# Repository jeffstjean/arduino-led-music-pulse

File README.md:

# Arduino Led Music Pulse

Controls an LED light-strip using an Arduino to pulse to the beat of a input from a 3.5mm audio device
[View the Demo.](https://youtu.be/wHUdtZS7I78)

## Getting Started
---

### Prerequisites

You will need to download the following libraries:
* [ArduinoFFT](https://github.com/kosme/arduinoFFT)
* [Adafruit_NeoPixel](https://github.com/adafruit/Adafruit_NeoPixel)
* [MicroSmooth](https://github.com/asheeshr/Microsmooth)

### Hardware

Read [HARDWARE.md](HARDWARE.md) to make sure you are using the correct parts.

### Schematic

Please reference [audio-in-schematic.png](audio-in-schematic.png) to connect the audio-in circuit correctly.  
For the light strip: 5V connects to Arduino/external 5V, GND to Arduino/external GND and DATA to Arduino's Digital Pin 6.

### Installing

Once you have downloaded the files and libraries, upload the code to your Arduino.  
You can then plug in your phone or computer to the 3.5mm audio jack.  
Provde power to your arduino and begin playing music.  

## Authors

* **Jeff St. Jean** - *Initial work* - [JeffStJean](https://github.com/jeffstjean)

## License

This project is licensed under the GNU v3 License - see the [LICENSE](LICENSE) file for details

## Acknowledgments

[Devon Crawford](https://www.youtube.com/channel/UCDrekHmOnkptxq3gUU0IyfA) for the inspiration for this project!  
[This StackExchange post](https://arduino.stackexchange.com/questions/25483/audio-input-into-a0) for help getting the voltage divider correctly wired.  
[This Arduino Forum post](https://forum.arduino.cc/index.php?topic=508537.0) for guidance.

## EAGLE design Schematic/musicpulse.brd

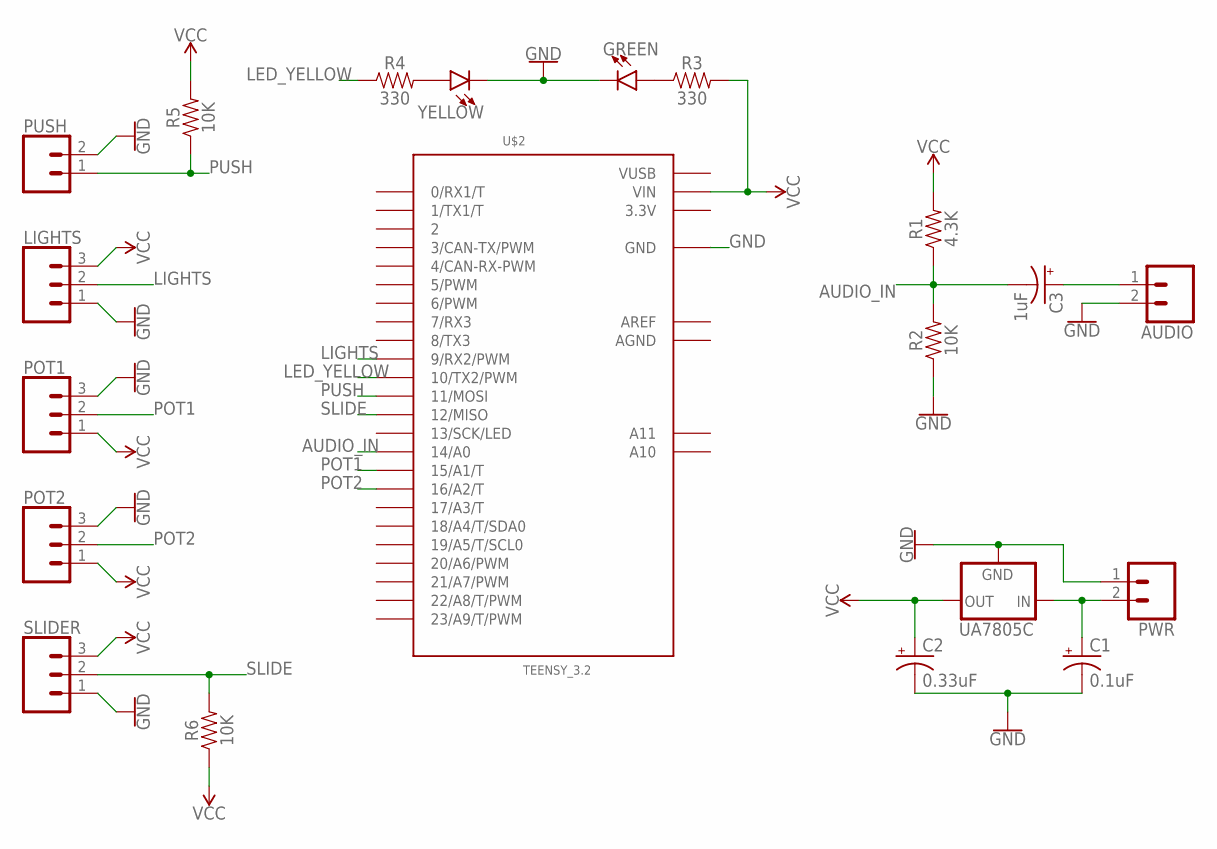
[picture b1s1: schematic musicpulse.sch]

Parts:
AUDIO: CONN_02; 1X02
C1: 0.1uF; CPOL-RADIAL-2.5MM-5MM
C2: 0.33uF; CPOL-RADIAL-2.5MM-5MM
C3: 1uF; CPOL-RADIAL-2.5MM-5MM
GREEN: LED-3MM-NO_SILK; LED_3MM-NS
LIGHTS: CONN_03; 1X03
POT1, POT2: CONN_03; 1X03
PUSH: CONN_02; 1X02
PWR: CONN_02; 1X02
R1: 4.3K; AXIAL-0.3
R2, R5, R6: 10K; AXIAL-0.3
R3, R4: 330; AXIAL-0.3
SLIDER: CONN_03; 1X03
U$2: TEENSY_3.2; TEENSY_3.0-3.2&LC_DIL+4
UA7805C: V_REG_78XXSINK; TO220-IGO
YELLOW: LED-3MM-NO_SILK; LED_3MM-NS

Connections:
3.3V: U$2.3.3V
AGND: U$2.AGND
AREF: U$2.AREF
AUDIO_IN: C3.2 (-), R1.P$1 (1), R2.P$2 (2), U$2.14/A0
GND: AUDIO.2, C1.2 (-), C2.2 (-), GREEN.K (C), LIGHTS.1, POT1.3, POT2.3, PUSH.2, PWR.1, R2.P$1 (1), SLIDER.1, U$2.GND, UA7805C.GND, YELLOW.K (C)
LED_YELLOW: R4.P$1 (1), U$2.10 (10/TX2/PWM)
LIGHTS: LIGHTS.2, U$2.9 (9/RX2/PWM)
unnamed: C1.1 (+), PWR.2, UA7805C.IN
unnamed: R4.P$2 (2), YELLOW.A
unnamed: GREEN.A, R3.P$1 (1)
unnamed: AUDIO.1, C3.1 (+)
POT1: POT1.2, U$2.15/A1 (15/A1/T)
POT2: POT2.2, U$2.16/A2 (16/A2/T)
PUSH: PUSH.1, R5.P$1 (1), U$2.11 (11/MOSI)
SLIDE: R6.P$2 (2), SLIDER.2, U$2.12 (12/MISO)
VCC: C2.1 (+), LIGHTS.3, POT1.1, POT2.1, R1.P$2 (2), R3.P$2 (2), R5.P$2 (2), R6.P$1 (1), SLIDER.3, U$2.VIN, UA7805C.OUT
VUSB: U$2.VUSB

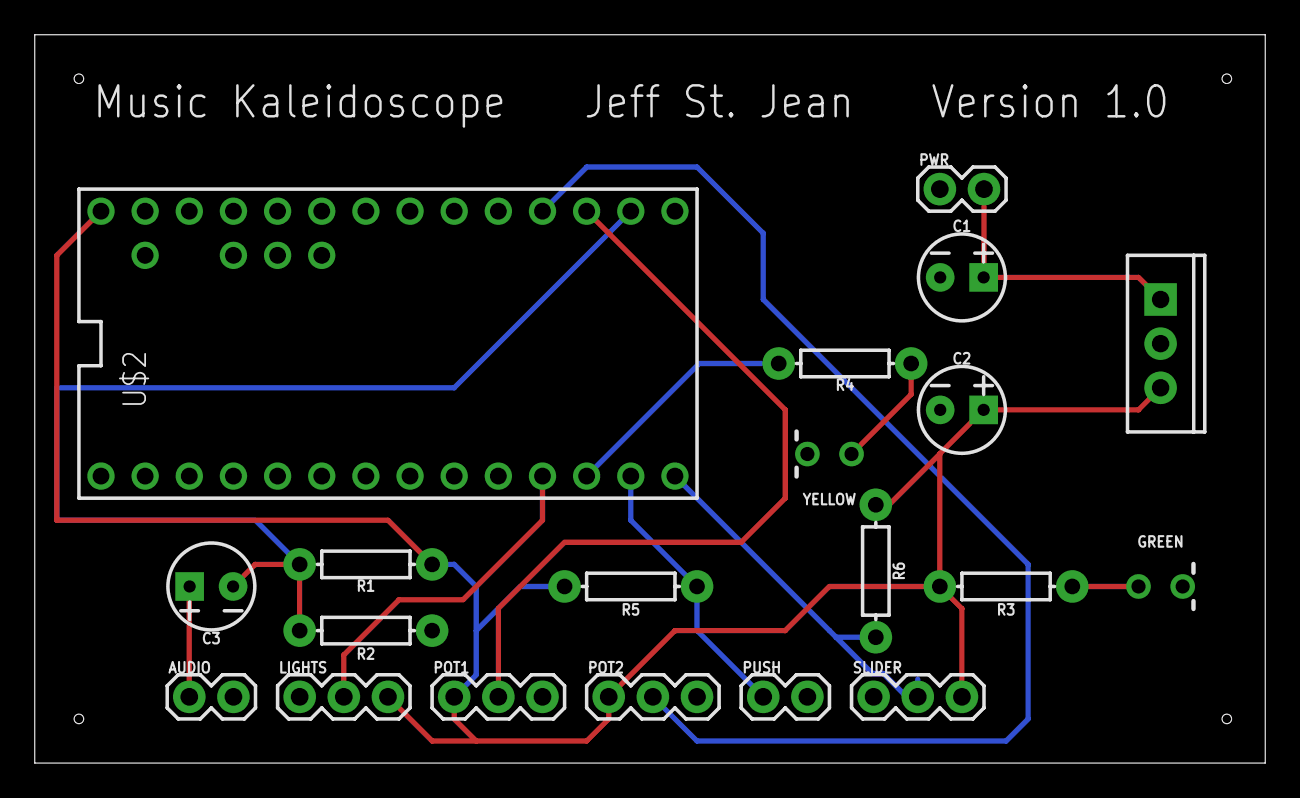
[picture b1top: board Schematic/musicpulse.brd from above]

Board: 2 copper layers, 70.8 x 41.9 mm, 20 parts (0 on the bottom side), 13 nets.

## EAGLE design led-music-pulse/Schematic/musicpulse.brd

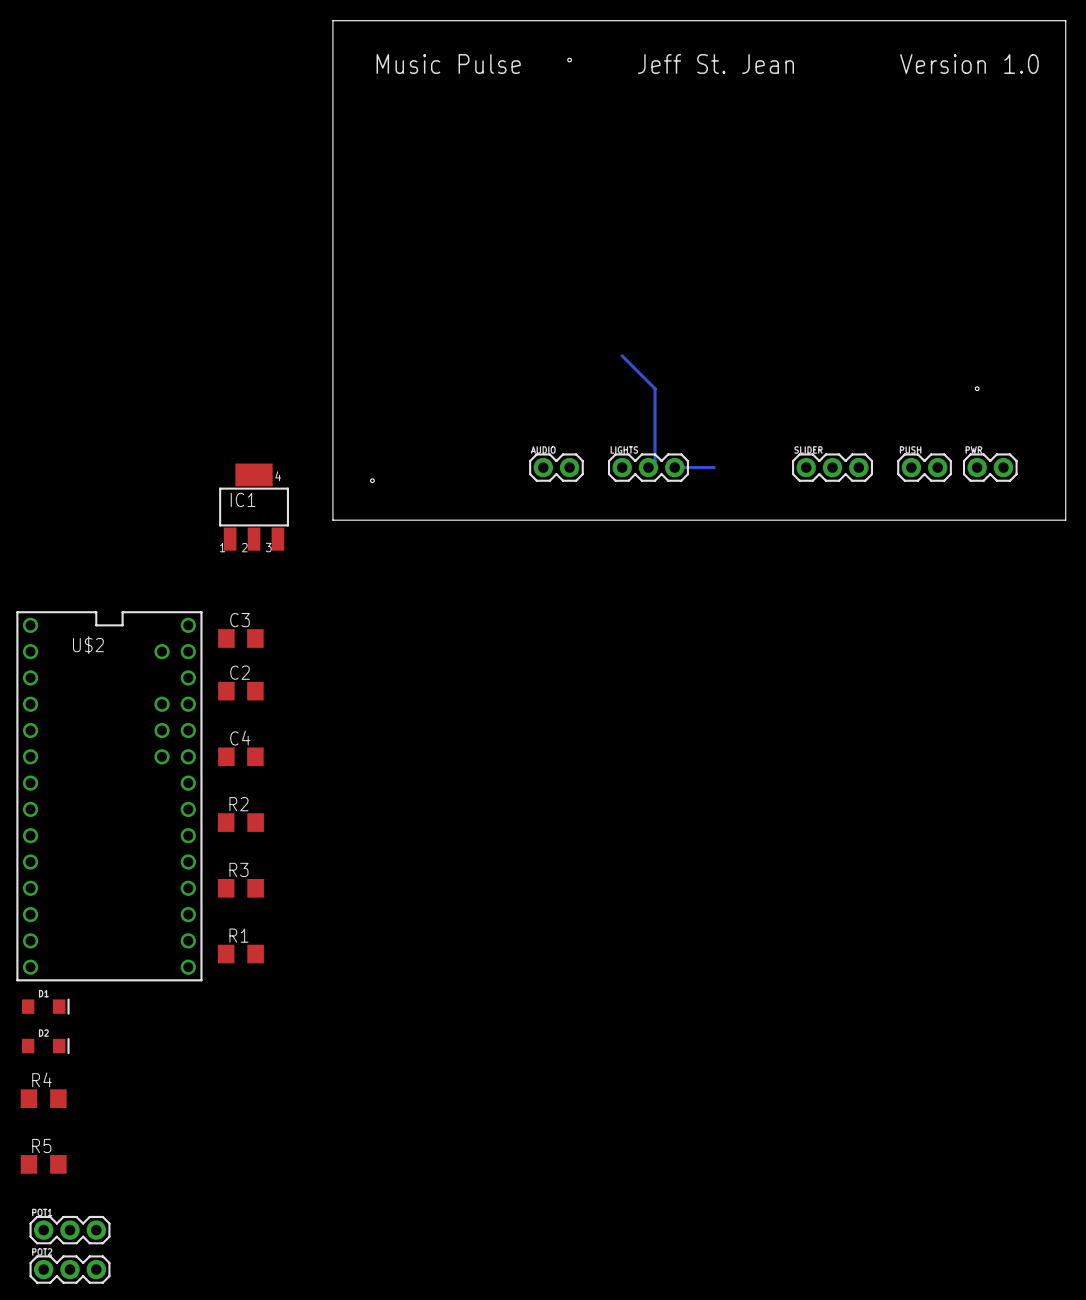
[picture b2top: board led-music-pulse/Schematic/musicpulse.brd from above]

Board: 2 copper layers, 70.8 x 48.2 mm, 19 parts (0 on the bottom side), 14 nets.

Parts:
AUDIO: 1X02
C2: 0.1uF; C1206
C3: 0.33uF; C1206
C4: 10uF; C1206
D1: GREEN; LED-1206
D2: Yellow; LED-1206
IC1: UA78M33DCY; SOT223
LIGHTS: 1X03
POT1, POT2: 1X03
PUSH: 1X02
PWR: 1X02
R1, R2, R3: 10k; R1206
R4, R5: 100; R1206
SLIDER: 1X03
U$2: TEENSY_3.1-3.2_DIL+4; TEENSY_3.0-3.2&LC_DIL+4

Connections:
AUDIO_IN: C4.1, R2.2, R3.1, U$2.14/A0
GND: AUDIO.2, C2.2, C3.2, D1.C, D2.C, IC1.2, IC1.4, LIGHTS.1, POT1.3, POT2.3, PUSH.2, PWR.1, R2.1, SLIDER.1, U$2.GND
LED_GREEN: C3.1, IC1.3, R4.1
LED_YELLOW: R5.2, U$2.10
LIGHTS: LIGHTS.2, U$2.9
unnamed: C2.1, IC1.1, PWR.2
unnamed: D1.A, R4.2
unnamed: D2.A, R5.1
unnamed: AUDIO.1, C4.2
POT1: POT1.2, U$2.15/A1
POT2: POT2.2, U$2.16/A2
PUSH: PUSH.1, R1.1, U$2.11
SLIDE: SLIDER.2, U$2.12
VCC: LIGHTS.3, POT1.1, POT2.1, R3.2, SLIDER.3, U$2.VIN

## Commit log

2018-12-02 Initial Commit.
2019-05-02 Eagle Schematic
2019-05-02 Manufacturing Files
2019-05-02 Updated Gerbers
2019-05-25 Added schematic
2019-07-14 Added gitignore
2019-07-14 Added files
2019-07-14 Backups
2019-07-16 Changed to through hole. Adjusted some resistor files. Rerouted board. Reprocessed gerbers. Added board and schematic reference pictures.
2019-07-18 Rerouted board. Added pullup to slider. Changed some resistor values.
2019-07-18 Added missing trace. Reprocessed CAM files.
2019-07-20 Adjusted slider trace
2019-07-20 Updated board image
2020-04-10 Added auto-transition between active and passive
    TODO: dire need of clean-up, reformatting and optimization

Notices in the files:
parts and their libraries:
SparkFun-Connectors: Licensing: Creative Commons ShareAlike 4.0 International - https://creativecommons.org/licenses/by-sa/4.0
